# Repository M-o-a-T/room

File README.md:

# Room controller

Initially planned for controlling a radiator, this mutated into a generic
room controller schematic, featuring

* ATmega 168 controller
* two 1wire slave interfaces
* one I²C interface
* two 24V outputs
  * low-side switched
  * diode protected
  * PWM capable
* four binary I/O wires
  * with ADC, if required
* on-board programming interface
  * 6-pin version, accessible with pogo-pin adapter
* optional XTAL for 20 MHz operation
* WAGO connectors for the bus wires

The board fits standard round wall outlets. Its height is nominally 13mm
(determined by the WAGO 243 connectors).

## Who needs two 1wire interfaces?

The idea is that one is used for "slow" operations (parasitic-powered
thermometers, firmware updates (yes, I plan to do that)), while the other
bus does the "fast" stuff (run a CONDITIONAL SEARCH ten times a second).

## No 1wire master? Why?

Timing. You cannot run a 1wire master and slave at the same time.
Not reliably in software on one MCU, anyway.

If you want a master, you have I²C, connect an I²C-to-1wire interface.
(No, I didn't reserve space on the board for this.)

## Why 5V instead of 3.3V?

That would require me to run 1wire on 3.3V. It's possible, but you have
much less noise resistance. Also, the ATmega168 won't do 20 MHz on 3.3V.

That being said, running just the I²C on 3.3V isn't too difficult,
I'll add that if and when somebody actually needs it.

## How about software support?

The board will be fully supported by OWFS and the library at
https://github.com/M-o-a-T/owslave .

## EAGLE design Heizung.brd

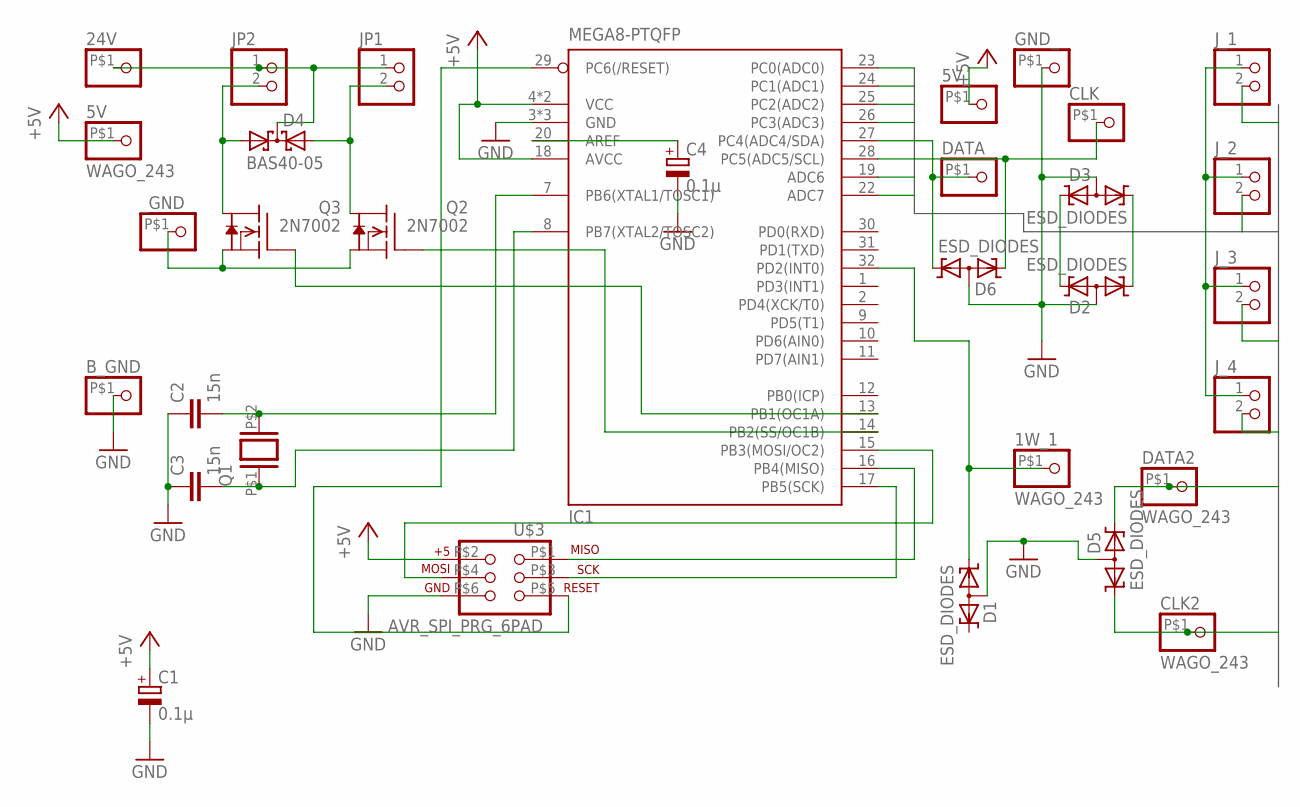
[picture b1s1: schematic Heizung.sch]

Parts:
1W_1, 5V, 5V_, 24V: WAGO_243
B_GND: WAGO_243
C1, C4: 0.1µ; CP1206
C2, C3: 15n; C0603
CLK, CLK2: WAGO_243
D1, D2, D3, D5, D6: ESD_DIODES; SOT23
D4: BAS40-05; SOT23
DATA, DATA2: WAGO_243
GND_: WAGO_243
IC1: MEGA8-PTQFP; TQFP32-08
JP1, JP2: PINHD-1X2LEVER; 1X02_GN
J_1, J_2, J_3, J_4: PINHD-1X2LEVER; 1X02_GN
Q1: XTALSMD5; Q_SMD5
Q2, Q3: 2N7002; SOT23
U$3: AVR_SPI_PRG_6PAD; 2X3_PAD
_GND: WAGO_243

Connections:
+5V: 5V.P$1, 5V_.P$1, C1.+, IC1.4 (VCC), IC1.6 (VCC), IC1.18 (AVCC), U$3.P$2 (2)
B1: D2.2 (K2), IC1.23 (PC0(ADC0)), J_1.2
B2: D2.1 (K1), IC1.24 (PC1(ADC1)), J_2.2
B3: D3.1 (K1), IC1.25 (PC2(ADC2)), J_3.2
B4: D3.2 (K2), IC1.26 (PC3(ADC3)), J_4.2
B5: D5.2 (K2), DATA2.P$1, IC1.19 (ADC6)
B6: CLK2.P$1, D5.1 (K1), IC1.22 (ADC7)
GND: B_GND.P$1, C1.-, C2.1, C3.1, C4.-, D1.3 (AA), D2.3 (AA), D3.3 (AA), D5.3 (AA), D6.3 (AA), GND_.P$1, IC1.3 (GND), IC1.5 (GND), IC1.21 (GND), J_1.1, J_2.1, J_3.1, J_4.1, U$3.P$6 (6)
GND24: Q2.2 (S), Q3.2 (S), _GND.P$1
unnamed: 24V.P$1, D4.3 (C), JP1.1, JP2.1
unnamed: IC1.14 (PB2(SS/OC1B)), Q2.1 (G)
unnamed: IC1.15 (PB3(MOSI/OC2)), U$3.P$4 (4)
unnamed: 1W_1.P$1, D1.1 (K1), IC1.32 (PD2(INT0))
unnamed: C2.2, IC1.7 (PB6(XTAL1/TOSC1)), Q1.P$2 (2)
unnamed: IC1.17 (PB5(SCK)), U$3.P$3 (3)
unnamed: D6.1 (K1), DATA.P$1, IC1.27 (PC4(ADC4/SDA))
unnamed: CLK.P$1, D6.2 (K2), IC1.28 (PC5(ADC5/SCL))
unnamed: D4.2 (A2), JP1.2, Q2.3 (D)
unnamed: C3.2, IC1.8 (PB7(XTAL2/TOSC2)), Q1.P$1 (1)
unnamed: D4.1 (A1), JP2.2, Q3.3 (D)
unnamed: IC1.16 (PB4(MISO)), U$3.P$1 (1)
unnamed: IC1.29 (PC6(/RESET)), U$3.P$5 (5)
unnamed: IC1.13 (PB1(OC1A)), Q3.1 (G)
unnamed: C4.+, IC1.20 (AREF)

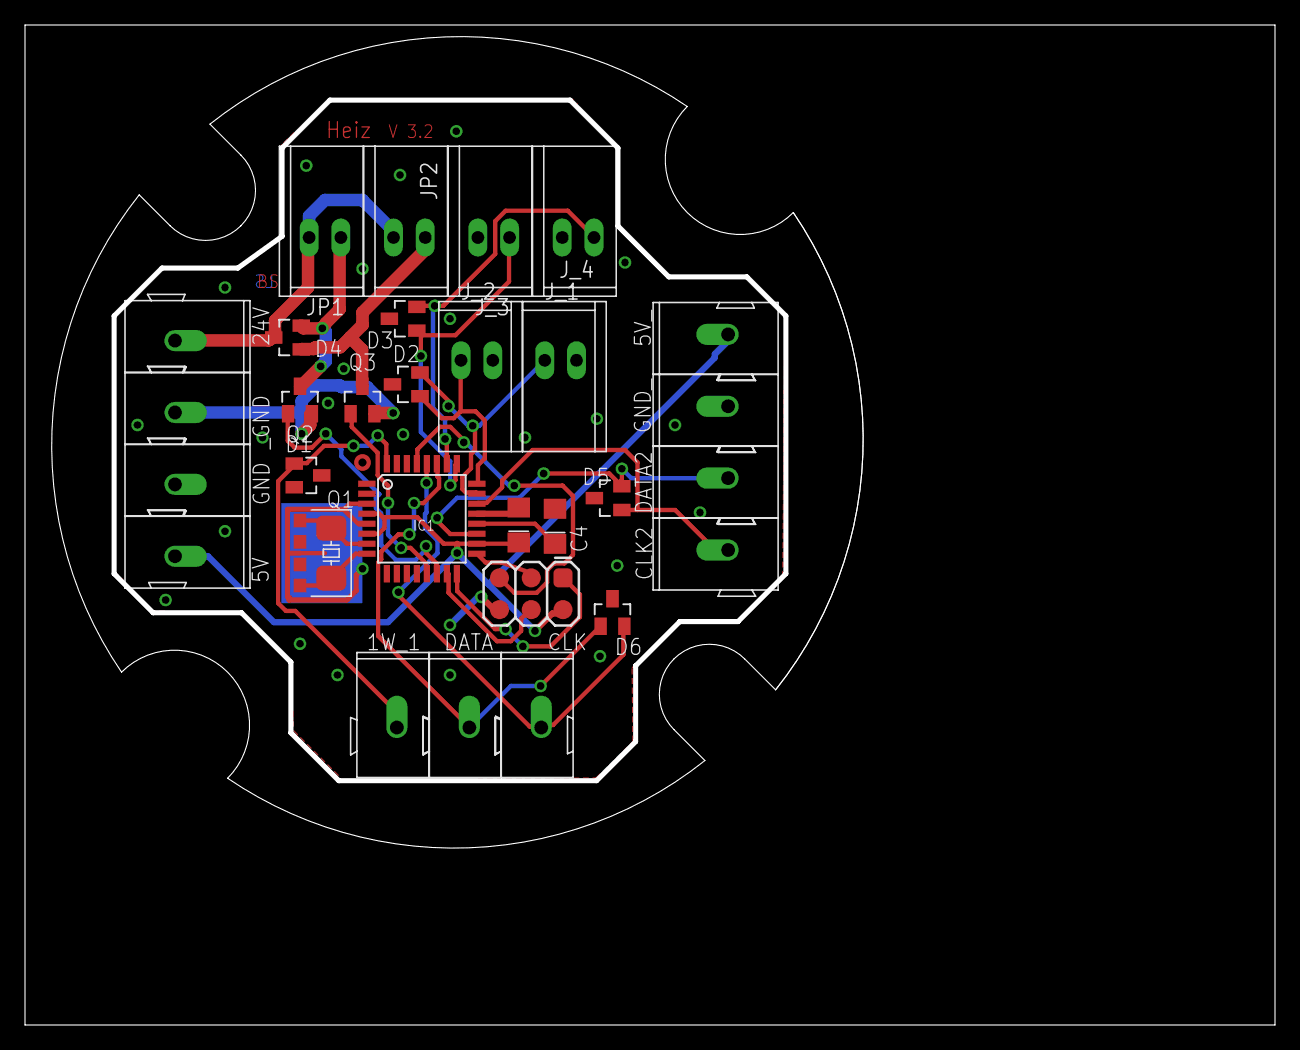
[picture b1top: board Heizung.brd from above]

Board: 2 copper layers, 100.0 x 80.0 mm, 33 parts (0 on the bottom side), 24 nets.

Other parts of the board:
U$1: UNTERPUTZDOSE

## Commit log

2015-02-21 Heizungssteuerung V2
    Pullups am i2c
2015-03-01 additional ground on power side, outline fixed
2015-03-24 Update auf 2.4
    2-Draht-Klemmen verwendet und gedreht
    Wagoklemmen nach innen gedreht
2015-03-24 Längere Pads für CPU
2015-04-26 V2.7: add diode (for switching relays)
    general clean-up
2015-04-26 change min width to 3.5mm, fix XTAL
2015-04-26 Floating wires are bad for you
2015-04-26 add README
2015-05-05 1x2 connectors wider, board outline more symmetric
2015-05-11 V2.9
    add capacitor to AREF
    better routing
2015-05-17 v3.0: use separate ground for switched power (24V)
    otherwise long cabling will raise ground too much
2015-06-03 V 3.2: secondary I²C yes, secondary 1wire no
